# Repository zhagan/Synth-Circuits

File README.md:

# Synth-Circuits
Eagle circuit designs for Eurorack Synthesis Systems<br>

<h2>Finished Projects: </h2><br>
<a href="https://github.com/zhagan/Synth-Circuits/tree/master/eagle/Dual%20XR-VCO">Dual XR VCO - dual VCO based on the XR-2206</a><br>
<a href="https://github.com/zhagan/Synth-Circuits/tree/master/eagle/euro%20buffered%20mult">Euro Buffered Mult - 1 -> 6 or 2x 1 -> 3 precision adjustable mult </a><br>
<a href="https://github.com/zhagan/Synth-Circuits/tree/master/eagle/euro%20mixer">EuroMixer - 6 -> 1 or 2x 3 -> 1 basic basic mixer for euro, can be made to boost</a><br>

<h2>Always hustlin':</h2><br>
Teensy Pedal / Eurorack mega interface<br>
V/O sequencing filter<br>
VCA for the masses<br>
My hyve clone<br>

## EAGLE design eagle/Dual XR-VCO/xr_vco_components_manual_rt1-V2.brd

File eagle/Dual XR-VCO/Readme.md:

This is a dual analog VCO made with the obsolete XR-2206 chip at it's core. As of now they are available from Tayda :

https://www.taydaelectronics.com/xr-2206-xr2206cp-xr2206-monolithic-function-generator-ic.html

BOM with some mouser parts and some Tayda. They only component not available from Tayda is the THAT300P it is a quad match transistor IC

You can experiment with using matched 3904s, I haven't gotten this to work, but I haven't tried:

https://docs.google.com/spreadsheets/d/1TqwrbGHlNdp3Y3I2KgH5bRB9O5VfACbchm6eOLaQew8/edit?usp=sharing

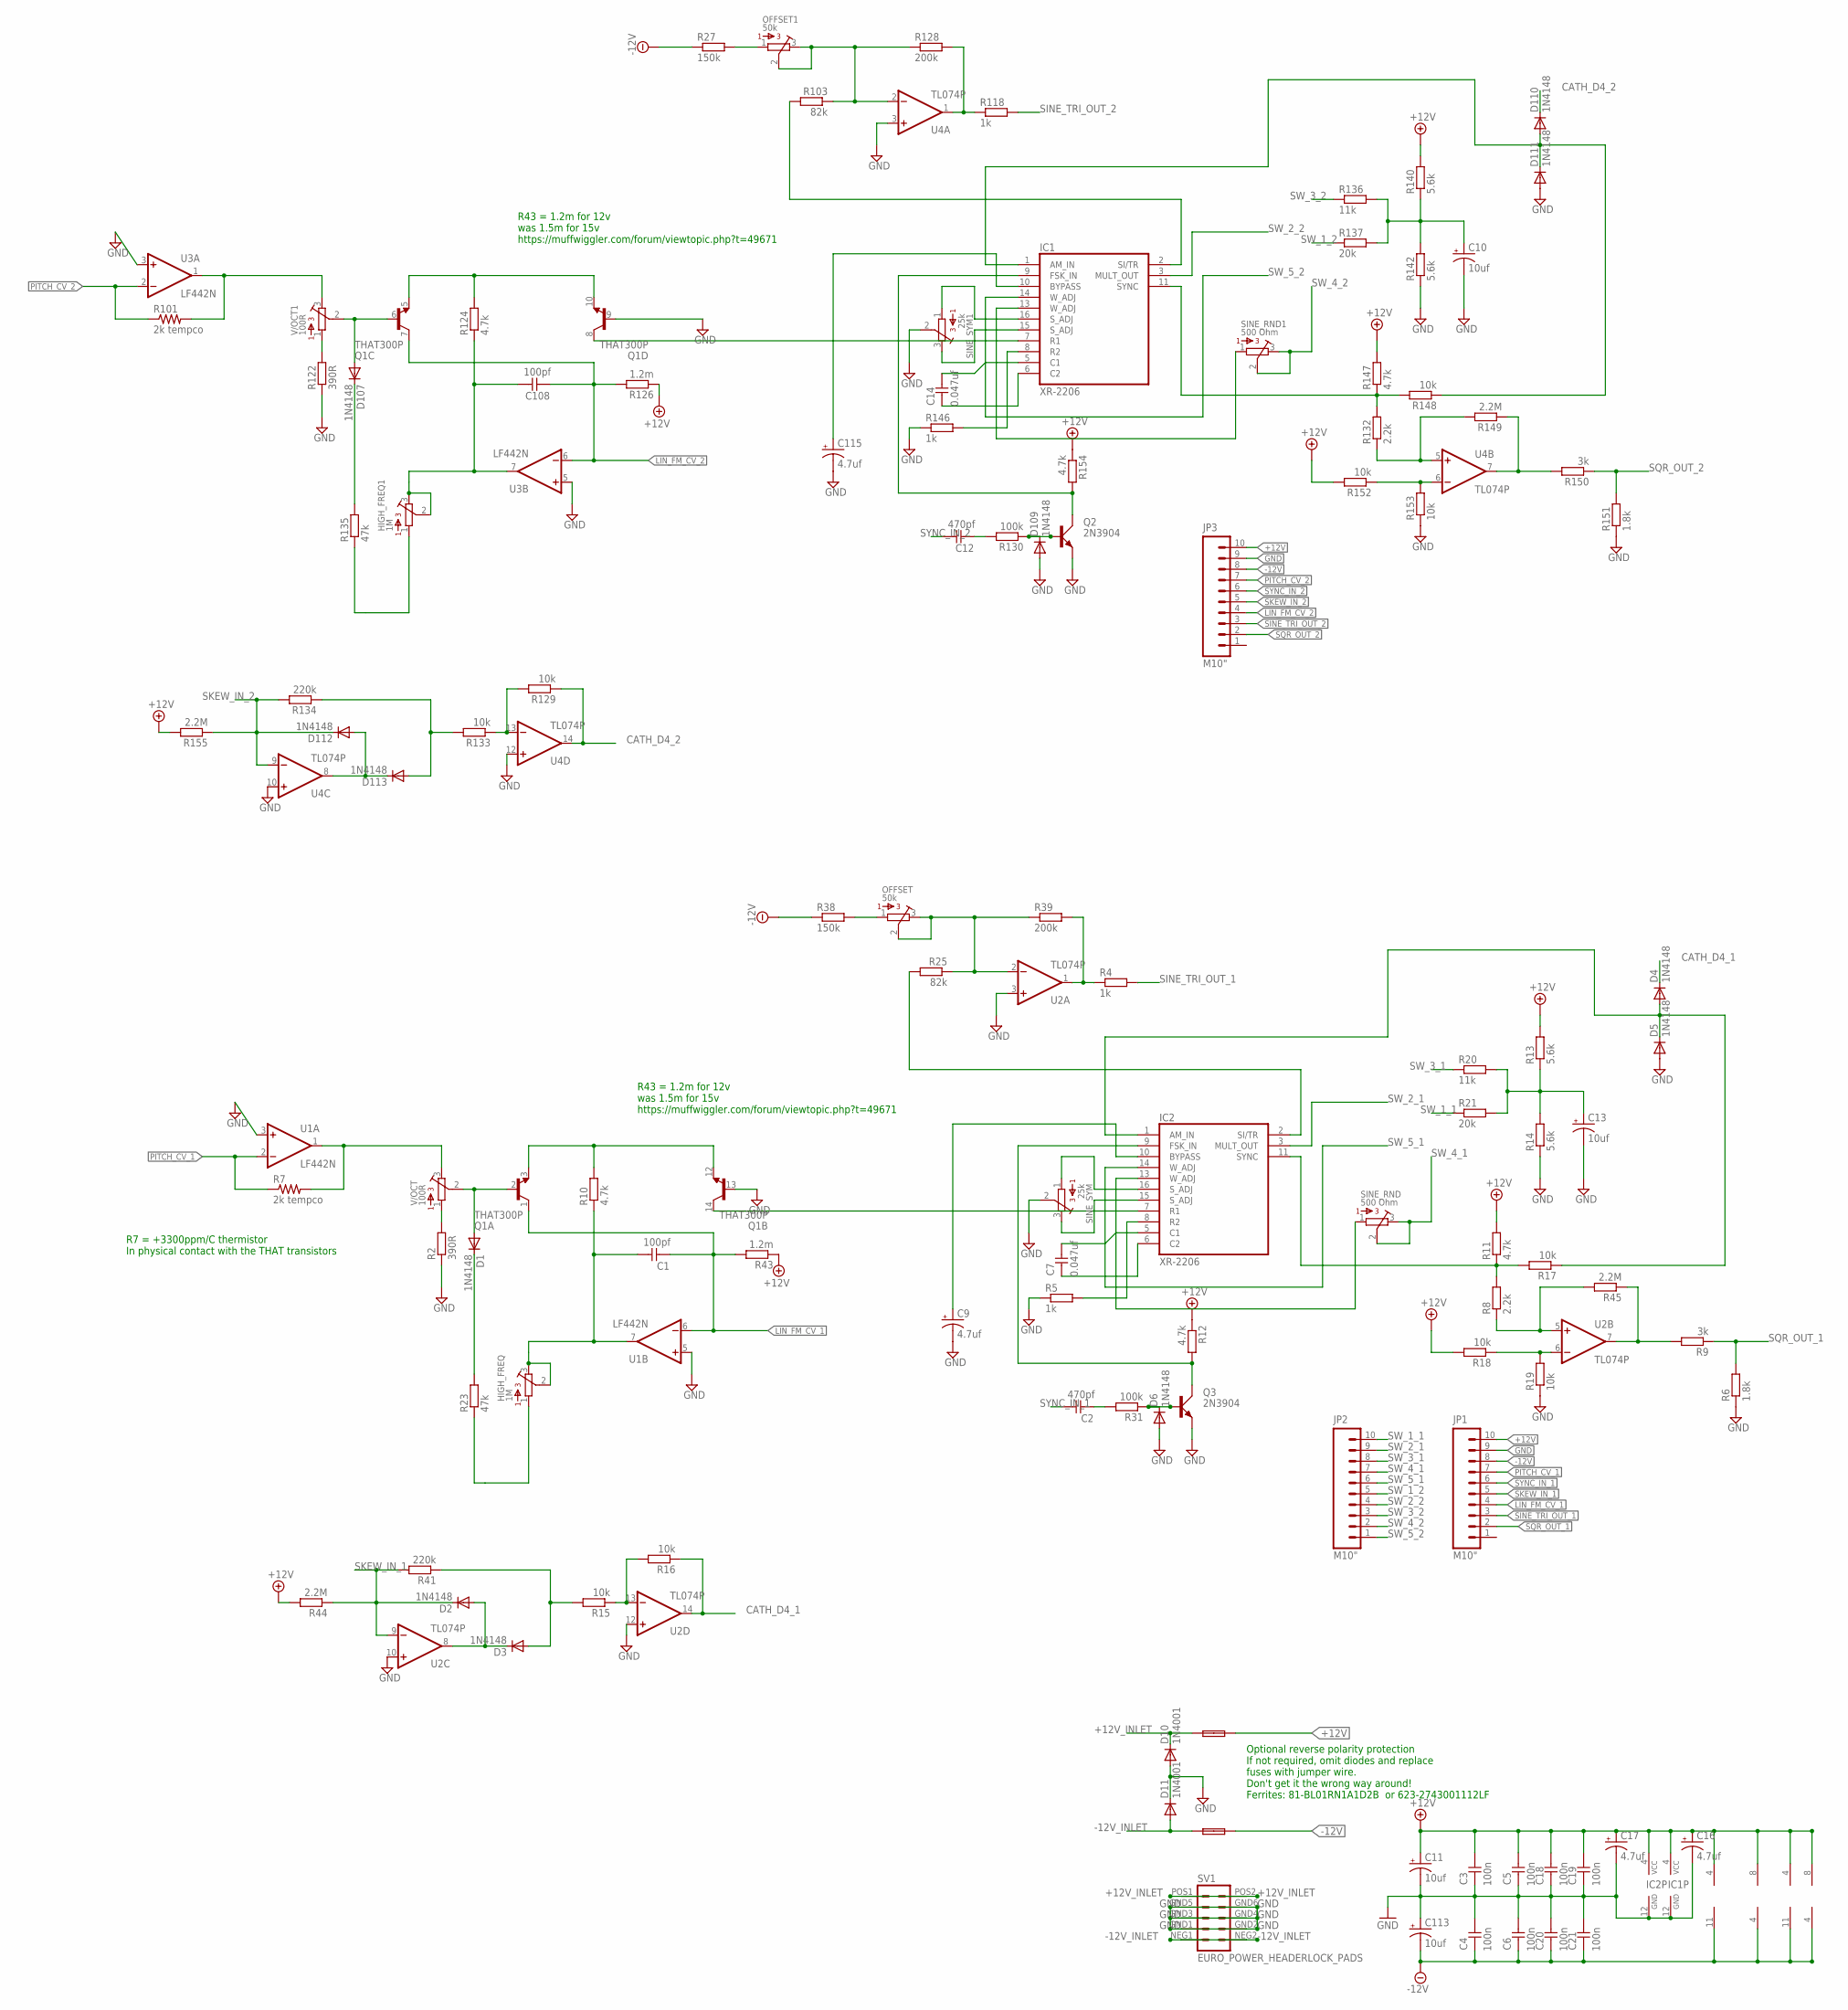
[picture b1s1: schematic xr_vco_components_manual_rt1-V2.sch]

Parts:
C1, C108: 100pf; C050-024X044
C2, C12: 470pf; C050-024X044
C3, C4, C5, C6, C18, C19, C20, C21: 100n; C050-024X044
C7, C14: 0.047uf; C050-024X044
C9, C16, C17, C115: 4.7uf; CPOL-RADIAL-10UF-25V
C10, C11, C13, C113: 10uf; CPOL-RADIAL-10UF-25V
D1, D2, D3, D4, D5, D6, D107, D109, D110, D111, D112, D113: 1N4148; DO35-7
D10, D11: 1N4001; DO41-10
F1, F2: FUSE; C050H075X075
HIGH_FREQ, HIGH_FREQ1: 1M; BOURNS_3362P_TRIMMER
IC1, IC2: XR-2206; DIL16
JP1, JP2, JP3: M10"; 1X10
OFFSET, OFFSET1: 50k; BOURNS_3362P_TRIMMER
Q1: THAT300P; DIL14
Q2, Q3: 2N3904; TO92D
R2, R122: 390R; 7MM_RESISTOR
R4, R5, R118, R146: 1k; 7MM_RESISTOR
R6, R151: 1.8k; 7MM_RESISTOR
R7, R101: 2k tempco; 0309/12
R8, R132: 2.2k; 7MM_RESISTOR
R9, R150: 3k; 7MM_RESISTOR
R10, R11, R12, R124, R147, R154: 4.7k; 7MM_RESISTOR
R13, R14, R140, R142: 5.6k; 7MM_RESISTOR
R15, R16, R17, R18, R19, R129, R133, R148, R152, R153: 10k; 7MM_RESISTOR
R20, R136: 11k; 7MM_RESISTOR
R21, R137: 20k; 7MM_RESISTOR
R23, R135: 47k; 7MM_RESISTOR
R25, R103: 82k; 7MM_RESISTOR
R27, R38: 150k; 7MM_RESISTOR
R31, R130: 100k; 7MM_RESISTOR
R39, R128: 200k; 7MM_RESISTOR
R41, R134: 220k; 7MM_RESISTOR
R43, R126: 1.2m; 7MM_RESISTOR
R44, R45, R149, R155: 2.2M; 7MM_RESISTOR
SINE_RND, SINE_RND1: 500 Ohm; BOURNS_3362P_TRIMMER
SINE_SYM, SINE_SYM1: 25k; BOURNS_3362P_TRIMMER
SV1: EURO_POWER_HEADERLOCK_PADS; EURO_PWR_HEADER_LOCK
U1, U3: LF442N; DIL08
U2, U4: TL074P; DIL14
V/OCT, V/OCT1: 100R; BOURNS_3362P_TRIMMER

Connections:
+12V: C3.1, C5.1, C11.1 (+), C16.1 (+), C17.1 (+), C18.1, C19.1, F1.2, IC1.4 (VCC), IC2.4 (VCC), JP1.10, JP3.10, R11.2, R12.1, R13.2, R18.2, R43.1, R44.2, R126.1, R140.2, R147.2, R152.2, R154.1, R155.2, U1.8 (V+), U2.4 (V+), U3.8 (V+), U4.4 (V+)
+12V_INLET: D10.C, F1.1, SV1.POS1 (10), SV1.POS2 (9)
-12V: C4.2, C6.2, C20.2, C21.2, C113.2 (-), F2.2, JP1.8, JP3.8, R27.1, R38.1, U1.4 (V-), U2.11 (V-), U3.4 (V-), U4.11 (V-)
-12V_INLET: D11.A, F2.1, SV1.NEG1 (2), SV1.NEG2 (1)
CATH_D4_1: D4.C, R16.1, U2.14 (OUT)
CATH_D4_2: D110.C, R129.1, U4.14 (OUT)
GND: C3.2, C4.1, C5.2, C6.1, C9.2 (-), C10.2 (-), C11.2 (-), C13.2 (-), C16.2 (-), C17.2 (-), C18.2, C19.2, C20.1, C21.1, C113.1 (+), C115.2 (-), D5.A, D6.A, D10.A, D11.C, D109.A, D111.A, IC1.12 (GND), IC2.12 (GND), JP1.9, JP3.9, Q1.9 (B), Q1.13 (B), Q2.E, Q3.E, R2.1, R5.1, R6.1, R14.1, R19.1, R122.1, R142.1, R146.1, R151.1, R153.1, SINE_SYM.2, SINE_SYM1.2, SV1.GND1 (4), SV1.GND2 (3), SV1.GND3 (6), SV1.GND4 (5), SV1.GND5 (8), SV1.GND6 (7), U1.3 (+IN), U1.5 (+IN), U2.3 (+IN), U2.10 (+IN), U2.12 (+IN), U3.3 (+IN), U3.5 (+IN), U4.3 (+IN), U4.10 (+IN), U4.12 (+IN)
LIN_FM_CV_1: C1.2, JP1.4, Q1.1 (C), R43.2, U1.6 (-IN)
LIN_FM_CV_2: C108.2, JP3.4, Q1.7 (C), R126.2, U3.6 (-IN)
unnamed: IC2.7 (R1), Q1.14 (C)
unnamed: D1.C, R23.2
unnamed: HIGH_FREQ.1, R23.1
unnamed: R101.2, U3.1 (OUT), V/OCT1.3
unnamed: IC2.2 (SI/TR), R25.2
unnamed: R122.2, V/OCT1.1
unnamed: R7.2, U1.1 (OUT), V/OCT.3
unnamed: OFFSET.2, OFFSET.3, R25.1, R39.1, U2.2 (-IN)
unnamed: R2.2, V/OCT.1
unnamed: D1.A, Q1.2 (B), V/OCT.2
unnamed: Q1.3 (E), Q1.12 (E), R10.2
unnamed: OFFSET.1, R38.2
unnamed: R4.1, R39.2, U2.1 (OUT)
unnamed: D107.A, Q1.6 (B), V/OCT1.2
unnamed: C1.1, HIGH_FREQ.2, HIGH_FREQ.3, R10.1, U1.7 (OUT)
unnamed: C13.1 (+), R13.1, R14.2, R20.2, R21.2
unnamed: IC2.16 (S_ADJ), SINE_SYM.1
unnamed: Q1.5 (E), Q1.10 (E), R124.2
unnamed: C108.1, HIGH_FREQ1.2, HIGH_FREQ1.3, R124.1, U3.7 (OUT)
unnamed: IC2.13 (W_ADJ), SINE_RND.1
unnamed: IC2.15 (S_ADJ), SINE_SYM.3
unnamed: IC2.8 (R2), R5.2
unnamed: R18.1, R19.2, U2.6 (-IN)
unnamed: R9.2, R45.1, U2.7 (OUT)
unnamed: R15.1, R16.2, U2.13 (-IN)
unnamed: R8.1, R45.2, U2.5 (+IN)
unnamed: D4.A, D5.C, IC2.1 (AM_IN), R17.1
unnamed: C2.2, R31.2
unnamed: D6.C, Q3.B, R31.1
unnamed: IC2.11 (SYNC), R8.2, R11.1, R17.2
unnamed: IC2.9 (FSK_IN), Q3.C, R12.2
unnamed: C7.2, IC2.6 (C2)
unnamed: C7.1, IC2.5 (C1)
unnamed: C9.1 (+), IC2.10 (BYPASS)
unnamed: D2.A, D3.C, U2.8 (OUT)
unnamed: D3.A, R15.2, R41.1
unnamed: IC1.7 (R1), Q1.8 (C)
unnamed: HIGH_FREQ1.1, R135.1
unnamed: D107.C, R135.2
unnamed: IC1.2 (SI/TR), R103.2
unnamed: OFFSET1.2, OFFSET1.3, R103.1, R128.1, U4.2 (-IN)
unnamed: OFFSET1.1, R27.2
unnamed: R118.1, R128.2, U4.1 (OUT)
unnamed: C10.1 (+), R136.2, R137.2, R140.1, R142.2
unnamed: IC1.13 (W_ADJ), SINE_RND1.1
unnamed: IC1.16 (S_ADJ), SINE_SYM1.1
unnamed: IC1.15 (S_ADJ), SINE_SYM1.3
unnamed: IC1.8 (R2), R146.2
unnamed: R152.1, R153.2, U4.6 (-IN)
unnamed: R149.1, R150.2, U4.7 (OUT)
unnamed: R132.1, R149.2, U4.5 (+IN)
unnamed: IC1.11 (SYNC), R132.2, R147.1, R148.2
unnamed: D110.A, D111.C, IC1.1 (AM_IN), R148.1
unnamed: C12.2, R130.2
unnamed: D109.C, Q2.B, R130.1
unnamed: IC1.9 (FSK_IN), Q2.C, R154.2
unnamed: C14.2, IC1.6 (C2)
unnamed: C14.1, IC1.5 (C1)
unnamed: R129.2, R133.1, U4.13 (-IN)
unnamed: D112.A, D113.C, U4.8 (OUT)
unnamed: D113.A, R133.2, R134.1
unnamed: C115.1 (+), IC1.10 (BYPASS)
PITCH_CV_1: JP1.7, R7.1, U1.2 (-IN)
PITCH_CV_2: JP3.7, R101.1, U3.2 (-IN)
SINE_TRI_OUT_1: JP1.3, R4.2
SINE_TRI_OUT_2: JP3.3, R118.2
SKEW_IN_1: D2.C, JP1.5, R41.2, R44.1, U2.9 (-IN)
SKEW_IN_2: D112.C, JP3.5, R134.2, R155.1, U4.9 (-IN)
SQR_OUT_1: JP1.2, R6.2, R9.1
SQR_OUT_2: JP3.2, R150.1, R151.2
SW_1_1: JP2.10, R21.1
SW_1_2: JP2.5, R137.1
SW_2_1: IC2.3 (MULT_OUT), JP2.9
SW_2_2: IC1.3 (MULT_OUT), JP2.4
SW_3_1: JP2.8, R20.1
SW_3_2: JP2.3, R136.1
SW_4_1: JP2.7, SINE_RND.2, SINE_RND.3
SW_4_2: JP2.2, SINE_RND1.2, SINE_RND1.3
SW_5_1: IC2.14 (W_ADJ), JP2.6
SW_5_2: IC1.14 (W_ADJ), JP2.1
SYNC_IN_1: C2.1, JP1.6
SYNC_IN_2: C12.1, JP3.6

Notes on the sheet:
R7 = +3300ppm/C thermistor In physical contact with the THAT transistors
R43 = 1.2m for 12v was 1.5m for 15v https://muffwiggler.com/forum/viewtopic.php?t=49671
Optional reverse polarity protection If not required, omit diodes and replace fuses with jumper wire. Don't get it the wrong way around! Ferrites: 81-BL01RN1A1D2B or 623-2743001112LF

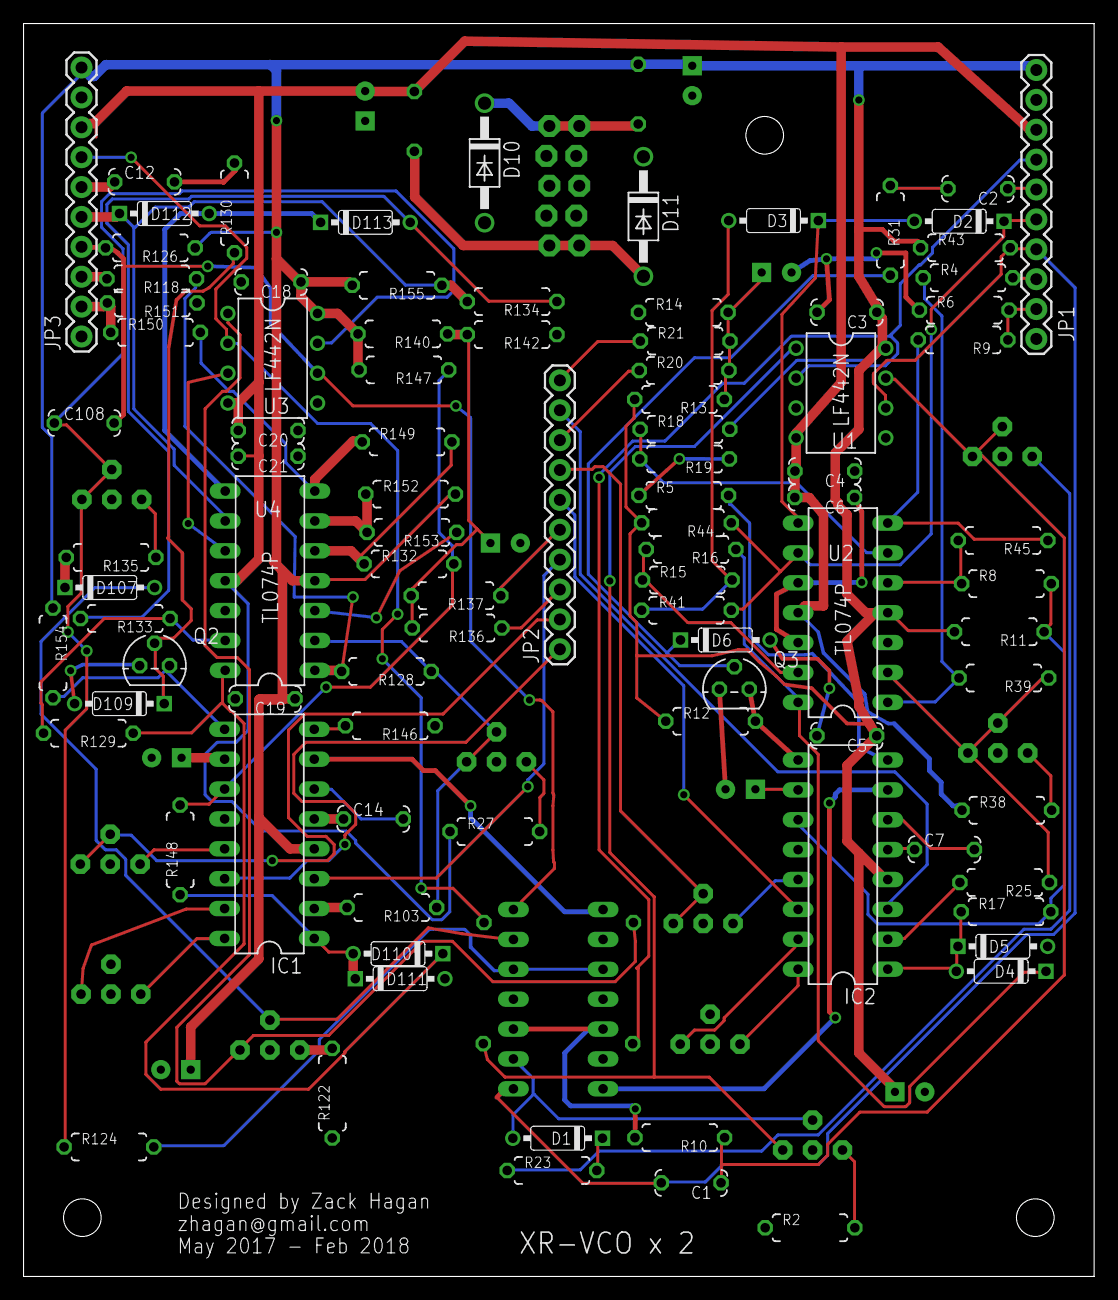
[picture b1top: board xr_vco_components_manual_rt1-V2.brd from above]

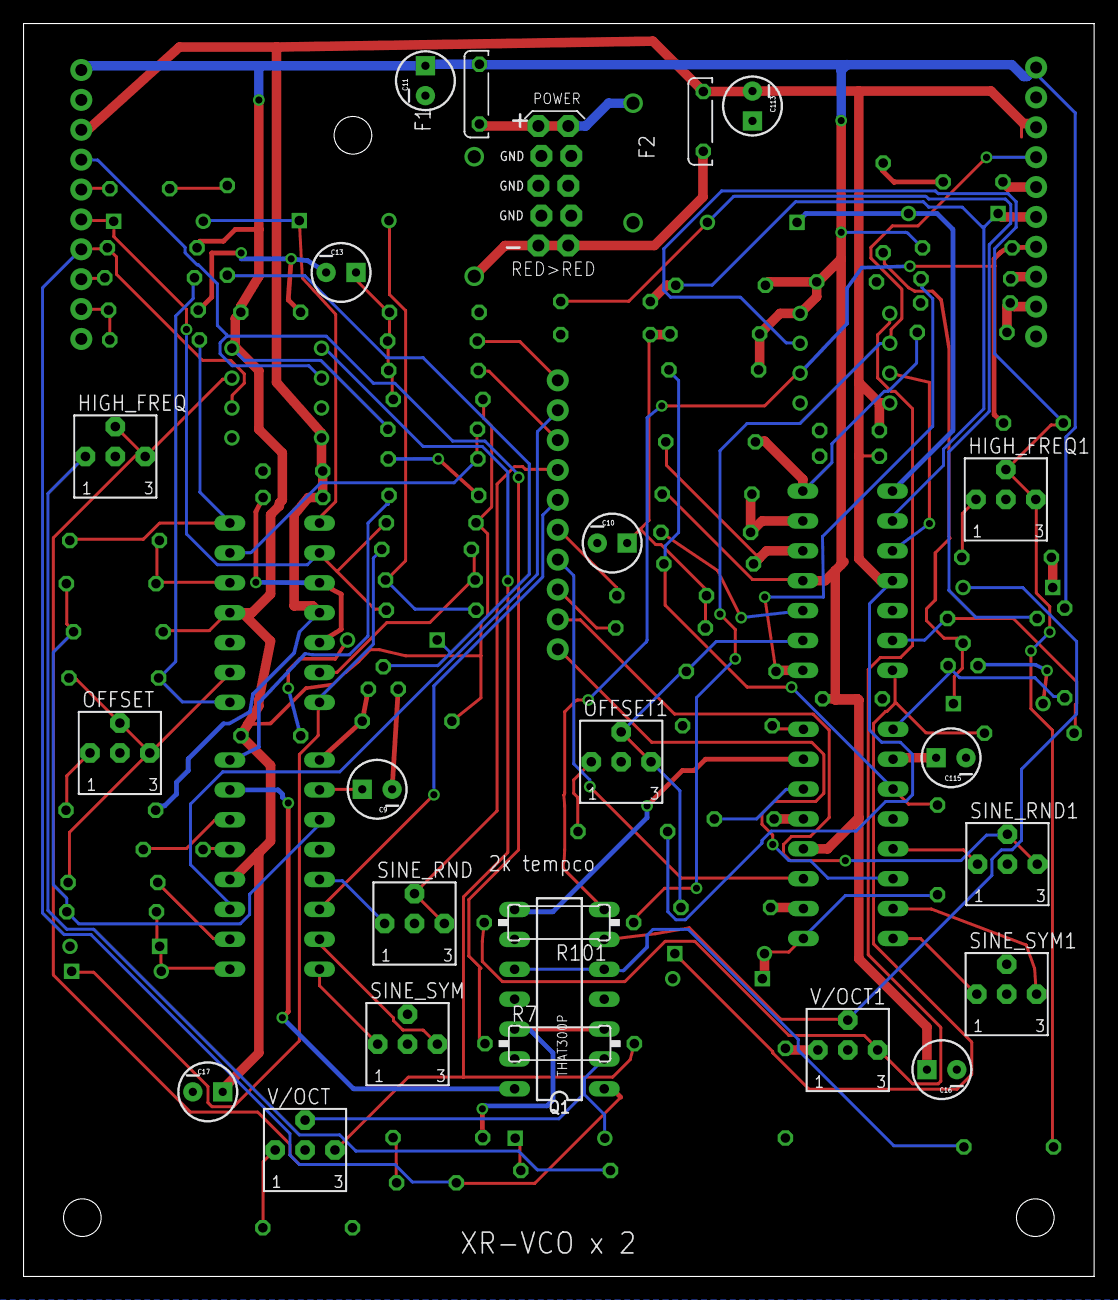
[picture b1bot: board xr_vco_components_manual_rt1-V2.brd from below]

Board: 2 copper layers, 91.0 x 106.5 mm, 120 parts (24 on the bottom side), 91 nets.

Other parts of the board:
U$1, U$2, U$3: MOUNTING_HOLE

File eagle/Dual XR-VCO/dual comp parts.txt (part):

Partlist

Exported from xr_vco_components_manual_rt1-V2.brd at 3/29/18 9:54 PM

EAGLE Version 7.3.0 Copyright (c) 1988-2015 CadSoft

Assembly variant: 

Part       Value                      Package              Library                 Position (mm)         Orientation

C1         100pf                      C050-024X044         TomW                    (56.75 7.96)          R180
C2         470pf                      C050-024X044         TomW                    (81.12 92.46)         R180
C3         100n                       C050-024X044         TomW                    (69.99 81.96)         R180
C4         100n                       C050-024X044         TomW                    (68.11 68.46)         R180
C5         100n                       C050-024X044         TomW                    (69.98 45.96)         R180
C6         100n                       C050-024X044         TomW                    (68.1 66.21)          R180
C7         0.047uf                    C050-024X044         TomW                    (78.28 36.29)         R0
C9         4.7uf                      CPOL-RADIAL-10UF-25V SparkFun-Passives       (60.94 41.41)         MR180
C10        10uf                       CPOL-RADIAL-10UF-25V SparkFun-Passives       (40.96 62.34)         MR0
C11        10uf                       CPOL-RADIAL-10UF-25V SparkFun-Passives       (56.84 101.64)        MR90
C12        470pf                      C050-024X044         TomW                    (10.29 93.04)         R0
C13        10uf                       CPOL-RADIAL-10UF-25V SparkFun-Passives       (64.01 85.34)         MR0
C14        0.047uf                    C050-024X044         TomW                    (29.74 38.89)         R0
C16        4.7uf                      CPOL-RADIAL-10UF-25V SparkFun-Passives       (12.94 17.58)         MR180
C17        4.7uf                      CPOL-RADIAL-10UF-25V SparkFun-Passives       (75.34 15.69)         MR0
C18        100n                       C050-024X044         TomW                    (21.04 84.54)         R180
C19        100n                       C050-024X044         TomW                    (20.54 49.1)          R180
C20        100n                       C050-024X044         TomW                    (20.79 71.91)         R180
C21        100n                       C050-024X044         TomW                    (20.79 69.72)         R180
C108       100pf                      C050-024X044         TomW                    (5.16 72.54)          R0
C113       10uf                       CPOL-RADIAL-10UF-25V SparkFun-Passives       (29.04 99.49)         MR270
C115       4.7uf                      CPOL-RADIAL-10UF-25V SparkFun-Passives       (12.16 44.09)         MR180
D1         1N4148                     DO35-7               MusicThingModular       (45.4 11.75)          R180
D2         1N4148                     DO35-7               MusicThingModular       (79.53 89.69)         R180
D3         1N4148                     DO35-7               MusicThingModular       (63.75 89.75)         R180
D4         1N4148                     DO35-7               MusicThingModular       (83.1 25.94)          R180
D5         1N4148                     DO35-7               MusicThingModular       (83.24 28.06)         R0
D6         1N4148                     DO35-7               MusicThingModular       (59.65 54.1)          R0
D10        1N4001                     DO41-10              diode                   (39.19 94.65)         R270
D11        1N4001                     DO41-10              diode                   (52.69 90.1)          R270
D107       1N4148                     DO35-7               MusicThingModular       (7.33 58.56)          R0
D109       1N4148                     DO35-7               MusicThingModular       (8.15 48.69)          R180
D110       1N4148                     DO35-7               MusicThingModular       (31.83 27.44)         R180
D111       1N4148                     DO35-7               MusicThingModular       (32.01 25.31)         R0
D112       1N4148                     DO35-7               MusicThingModular       (11.97 90.35)         R0
D113       1N4148                     DO35-7               MusicThingModular       (29.06 89.6)          R0
F1         FUSE                       C050H075X075         TomW                    (52.25 100.5)         MR90
F2         FUSE                       C050H075X075         TomW                    (33.22 98.18)         MR90
HIGH_FREQ  1M                         BOURNS_3362P_TRIMMER MusicThingModular       (83.2 69.7)           MR0
HIGH_FREQ1 1M                         BOURNS_3362P_TRIMMER MusicThingModular       (7.5 66.05)           MR0
IC1        XR-2206                    DIL16                exar                    (20.9 37.62)          R90
IC2        XR-2206                    DIL16                exar                    (69.65 35.01)         R90
JP1        M10"                       1X10                 SparkFun-Connectors     (86.09 79.69)         R90
JP2        M10"                       1X10                 SparkFun-Connectors     (45.59 53.31)         R90
JP3        M10"                       1X10                 SparkFun-Connectors     (4.93 79.9)           R90
OFFSET     50k                        BOURNS_3362P_TRIMMER MusicThingModular       (82.81 44.5)          MR0
OFFSET1    50k                        BOURNS_3362P_TRIMMER MusicThingModular       (40.2 43.75)          MR0
Q1         THAT300P                   DIL14                that-corp               (45.45 23.57)         MR90
Q2         2N3904                     TO92D                transistor-small-signal (11.14 51.92)         R0
Q3         2N3904                     TO92D                transistor-small-signal (60.42 49.92)         R0
R2         390R                       7MM_RESISTOR         MusicThingModular       (66.85 4.14)          R0
R4         1k                         7MM_RESISTOR         MusicThingModular       (80.28 84.89)         R0
R5         1k                         7MM_RESISTOR         MusicThingModular       (56.12 66.39)         R0
R6         1.8k                       7MM_RESISTOR         MusicThingModular       (79.96 82.14)         R0
R7         2k tempco                  0309/12              resistor                (45.43 19.79)         MR0
R8         2.2k                       7MM_RESISTOR         MusicThingModular       (83.55 58.89)         R0
R9         3k                         7MM_RESISTOR         MusicThingModular       (79.86 79.61)         R180
R10        4.7k                       7MM_RESISTOR         MusicThingModular       (55.78 11.8)          R180
R11        4.7k                       7MM_RESISTOR         MusicThingModular       (82.94 54.8)          R180
R12        4.7k                       7MM_RESISTOR         MusicThingModular       (58.4 47.2)           R0
R13        5.6k                       7MM_RESISTOR         MusicThingModular       (55.76 74.55)         R180
R14        5.6k                       7MM_RESISTOR         MusicThingModular       (56.08 81.95)         R0
R15        10k                        7MM_RESISTOR         MusicThingModular       (56.42 59.2)          R0
R16        10k                        7MM_RESISTOR         MusicThingModular       (56.74 61.8)          R180
R17        10k                        7MM_RESISTOR         MusicThingModular       (83.51 31)            R0
R18        10k                        7MM_RESISTOR         MusicThingModular       (56.22 72.01)         R0
R19        10k                        7MM_RESISTOR         MusicThingModular       (56.19 69.49)         R180
R20        11k                        7MM_RESISTOR         MusicThingModular       (56.15 77.01)         R0
R21        20k                        7MM_RESISTOR         MusicThingModular       (56.24 79.51)         R0
R23        47k                        7MM_RESISTOR         MusicThingModular       (44.92 9.01)          R0
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
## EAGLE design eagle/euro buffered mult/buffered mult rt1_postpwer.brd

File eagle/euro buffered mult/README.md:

Adjustable Precision Buffered Multiple
for Eurorack Synthesis Systems

Designed by Zack Hagan Feb 2018

This buffered mult is adjusted by a trimmer potentiometer on the front panel
to either exactly represent the original signal or slight amplify or attenuate
the original. This can be useful for getting VCOs pitch to track correctly,
especially when stacked with other VCOs.

BOM is all available from Mouser, except for the jacks - Thonk, Modular Addict,
Synthcube, or your local modular shop!

BOM:
https://docs.google.com/spreadsheets/d/19GKfh47OcOxOysG6X3gQdYsFXlBei4o8IAX7ovioopE/edit?usp=sharing

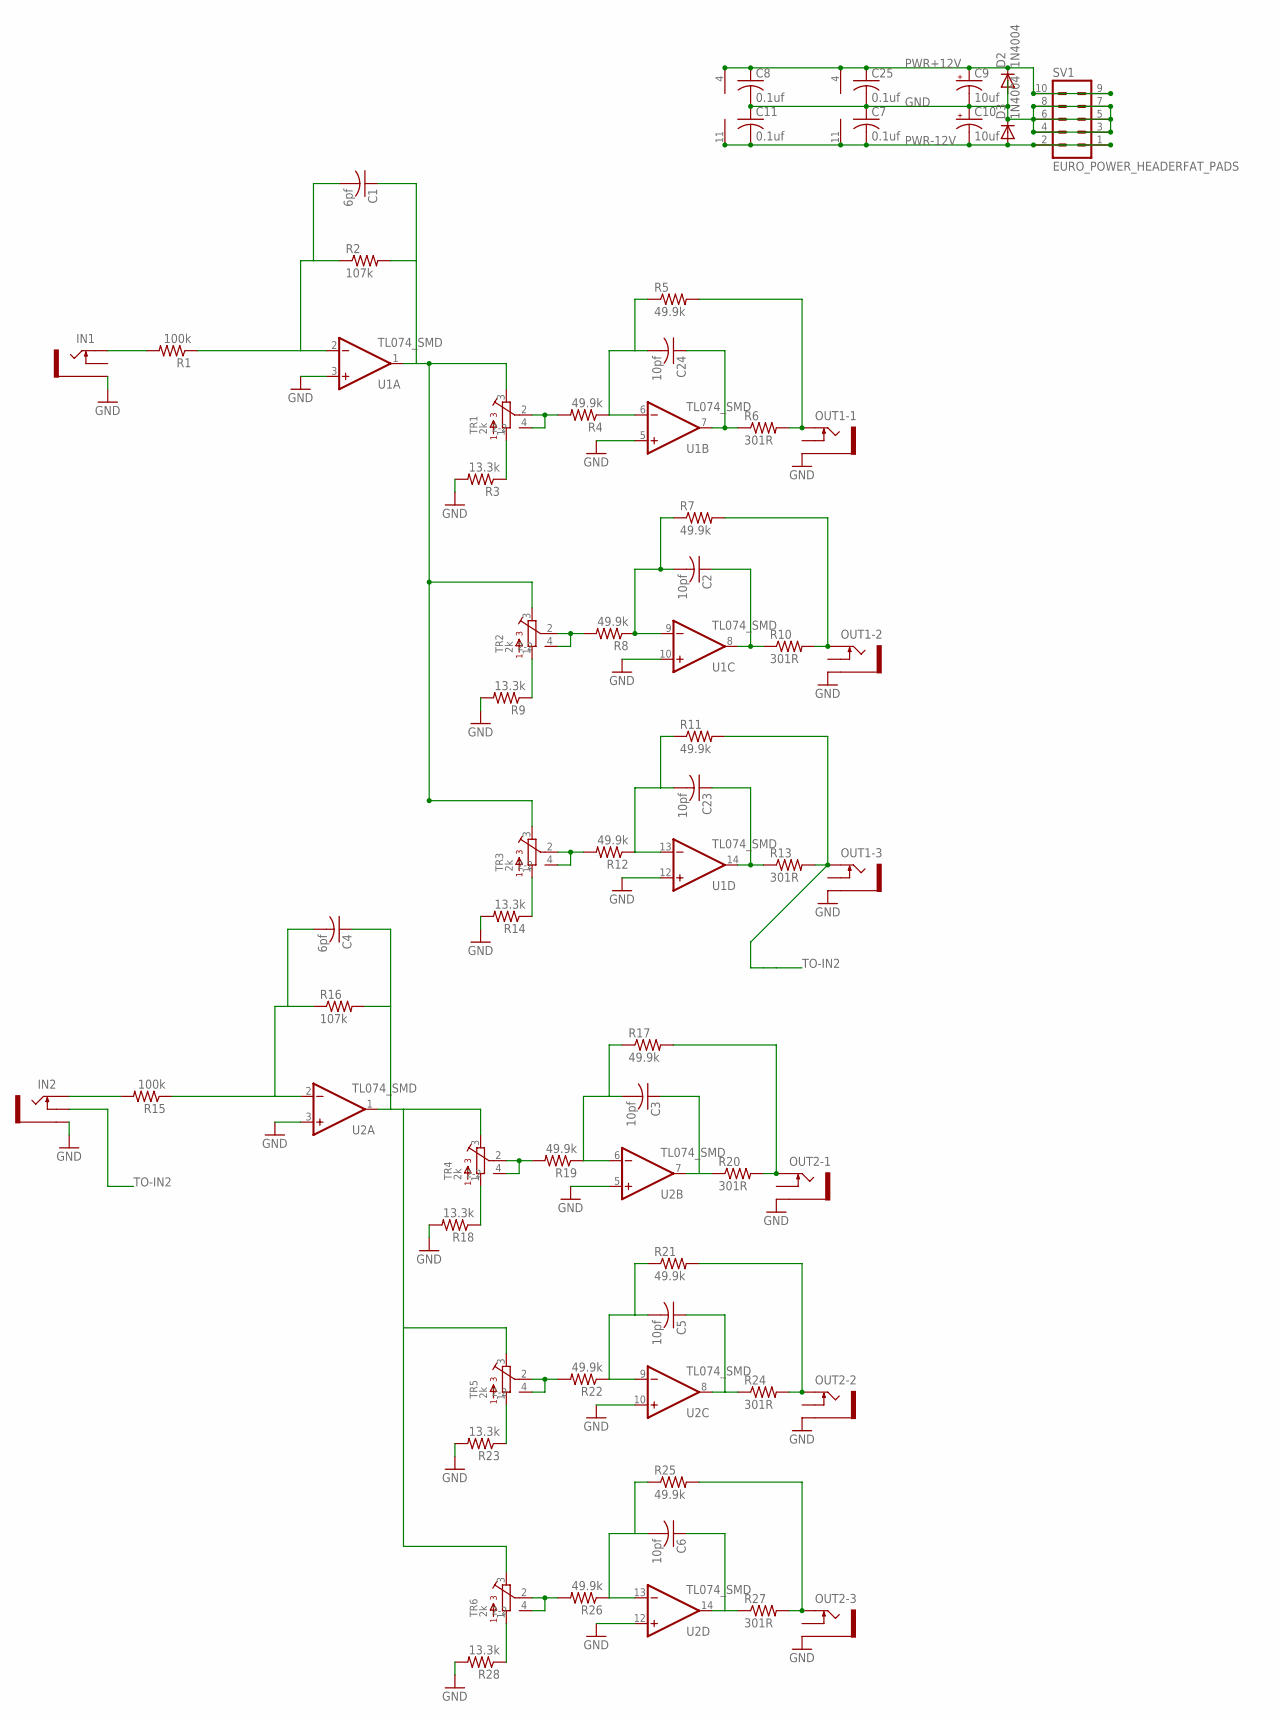
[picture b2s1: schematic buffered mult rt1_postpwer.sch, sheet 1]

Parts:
C1, C4: 6pf; C0603
C2, C3, C5, C6, C23, C24: 10pf; C0603
C7, C8, C11, C25: 0.1uf; C0603
C9, C10: 10uf; 153CLV-0505
D2, D3: 1N4004; DO41-10
IN1, IN2: THONKICONNNEW; WQP-PJ301M-12_JACK
OUT1-1, OUT1-2, OUT1-3, OUT2-1, OUT2-2, OUT2-3: THONKICONNNEW; WQP-PJ301M-12_JACK
R1, R15: 100k; R0603
R2, R16: 107k; R0603
R3, R9, R14, R18, R23, R28: 13.3k; R0603
R4, R5, R7, R8, R11, R12, R17, R19, R21, R22, R25, R26: 49.9k; R0603
R6, R10, R13, R20, R24, R27: 301R; R0603
SV1: EURO_POWER_HEADERFAT_PADS; EURO_PWR_HEADER_FAT
TR1, TR2, TR3, TR4, TR5, TR6: 2k; BOURNS_3362P_TRIMMER
U1, U2: TL074_SMD; SO14

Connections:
GND: C7.1, C8.2, C9.-, C10.+, C11.1, C25.2, D2.A, D3.C, IN1.P$3_SLEEVE (SLEEVE), IN2.P$3_SLEEVE (SLEEVE), OUT1-1.P$3_SLEEVE (SLEEVE), OUT1-2.P$3_SLEEVE (SLEEVE), OUT1-3.P$3_SLEEVE (SLEEVE), OUT2-1.P$3_SLEEVE (SLEEVE), OUT2-2.P$3_SLEEVE (SLEEVE), OUT2-3.P$3_SLEEVE (SLEEVE), R3.2, R9.2, R14.2, R18.2, R23.2, R28.2, SV1.3, SV1.4, SV1.5, SV1.6, SV1.7, SV1.8, U1.3 (+IN), U1.5 (+IN), U1.10 (+IN), U1.12 (+IN), U2.3 (+IN), U2.5 (+IN), U2.10 (+IN), U2.12 (+IN)
unnamed: IN1.P$1_TIP (TIP), R1.2
unnamed: C4.1, R16.2, TR4.3, TR5.3, TR6.3, U2.1 (OUT)
unnamed: C1.2, R1.1, R2.1, U1.2 (-IN)
unnamed: C4.2, R15.1, R16.1, U2.2 (-IN)
unnamed: R18.1, TR4.1
unnamed: R3.1, TR1.1
unnamed: C1.1, R2.2, TR1.3, TR2.3, TR3.3, U1.1 (OUT)
unnamed: R19.2, TR4.2, TR4.4 (2-2)
unnamed: R4.2, TR1.2, TR1.4 (2-2)
unnamed: C24.2, R4.1, R5.1, U1.6 (-IN)
unnamed: C3.2, R17.1, R19.1, U2.6 (-IN)
unnamed: C24.1, R6.1, U1.7 (OUT)
unnamed: OUT1-1.P$1_TIP (TIP), R5.2, R6.2
unnamed: C3.1, R20.1, U2.7 (OUT)
unnamed: R9.1, TR2.1
unnamed: OUT2-1.P$1_TIP (TIP), R17.2, R20.2
unnamed: R23.1, TR5.1
unnamed: R22.2, TR5.2, TR5.4 (2-2)
unnamed: R8.2, TR2.2, TR2.4 (2-2)
unnamed: C2.2, R7.1, R8.1, U1.9 (-IN)
unnamed: C2.1, R10.1, U1.8 (OUT)
unnamed: C5.2, R21.1, R22.1, U2.9 (-IN)
unnamed: C5.1, R24.1, U2.8 (OUT)
unnamed: OUT1-2.P$1_TIP (TIP), R7.2, R10.2
unnamed: OUT2-2.P$1_TIP (TIP), R21.2, R24.2
unnamed: R28.1, TR6.1
unnamed: R26.2, TR6.2, TR6.4 (2-2)
unnamed: C6.2, R25.1, R26.1, U2.13 (-IN)
unnamed: C6.1, R27.1, U2.14 (OUT)
unnamed: OUT2-3.P$1_TIP (TIP), R25.2, R27.2
unnamed: R14.1, TR3.1
unnamed: R12.2, TR3.2, TR3.4 (2-2)
unnamed: C23.2, R11.1, R12.1, U1.13 (-IN)
PWR+12V: C8.1, C9.+, C25.1, D2.C, SV1.9, SV1.10, U1.4 (V+), U2.4 (V+)
PWR-12V: C7.2, C10.-, C11.2, D3.A, SV1.1, SV1.2, U1.11 (V-), U2.11 (V-)
TO-IN2: C23.1, IN2.P$2_SWITCH (SWITCH), OUT1-3.P$1_TIP (TIP), R11.2, R13.1, R13.2, U1.14 (OUT)
TO-IN3: IN2.P$1_TIP (TIP), R15.2

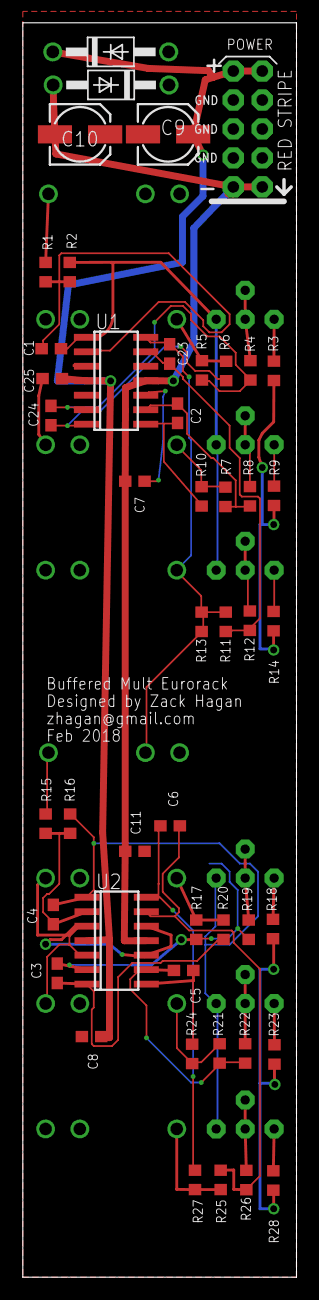
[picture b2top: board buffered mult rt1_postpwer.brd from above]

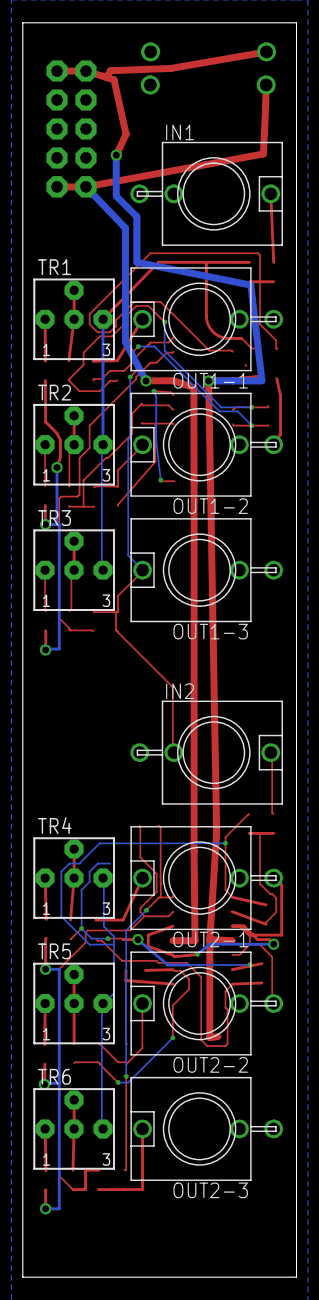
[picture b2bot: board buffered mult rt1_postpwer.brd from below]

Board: 2 copper layers, 24.0 x 110.0 mm, 61 parts (14 on the bottom side), 38 nets.

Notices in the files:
parts and their libraries:
SparkFun-Passives: Licensing: CC v3.0 Share-Alike You are welcome to use this library for commercial purposes.
that-corp: Copyright (C) 2008-2010, Bob Starr
SparkFun-LED: Licensing: Creative Commons ShareAlike 4.0 International - https://creativecommons.org/licenses/by-sa/4.0
